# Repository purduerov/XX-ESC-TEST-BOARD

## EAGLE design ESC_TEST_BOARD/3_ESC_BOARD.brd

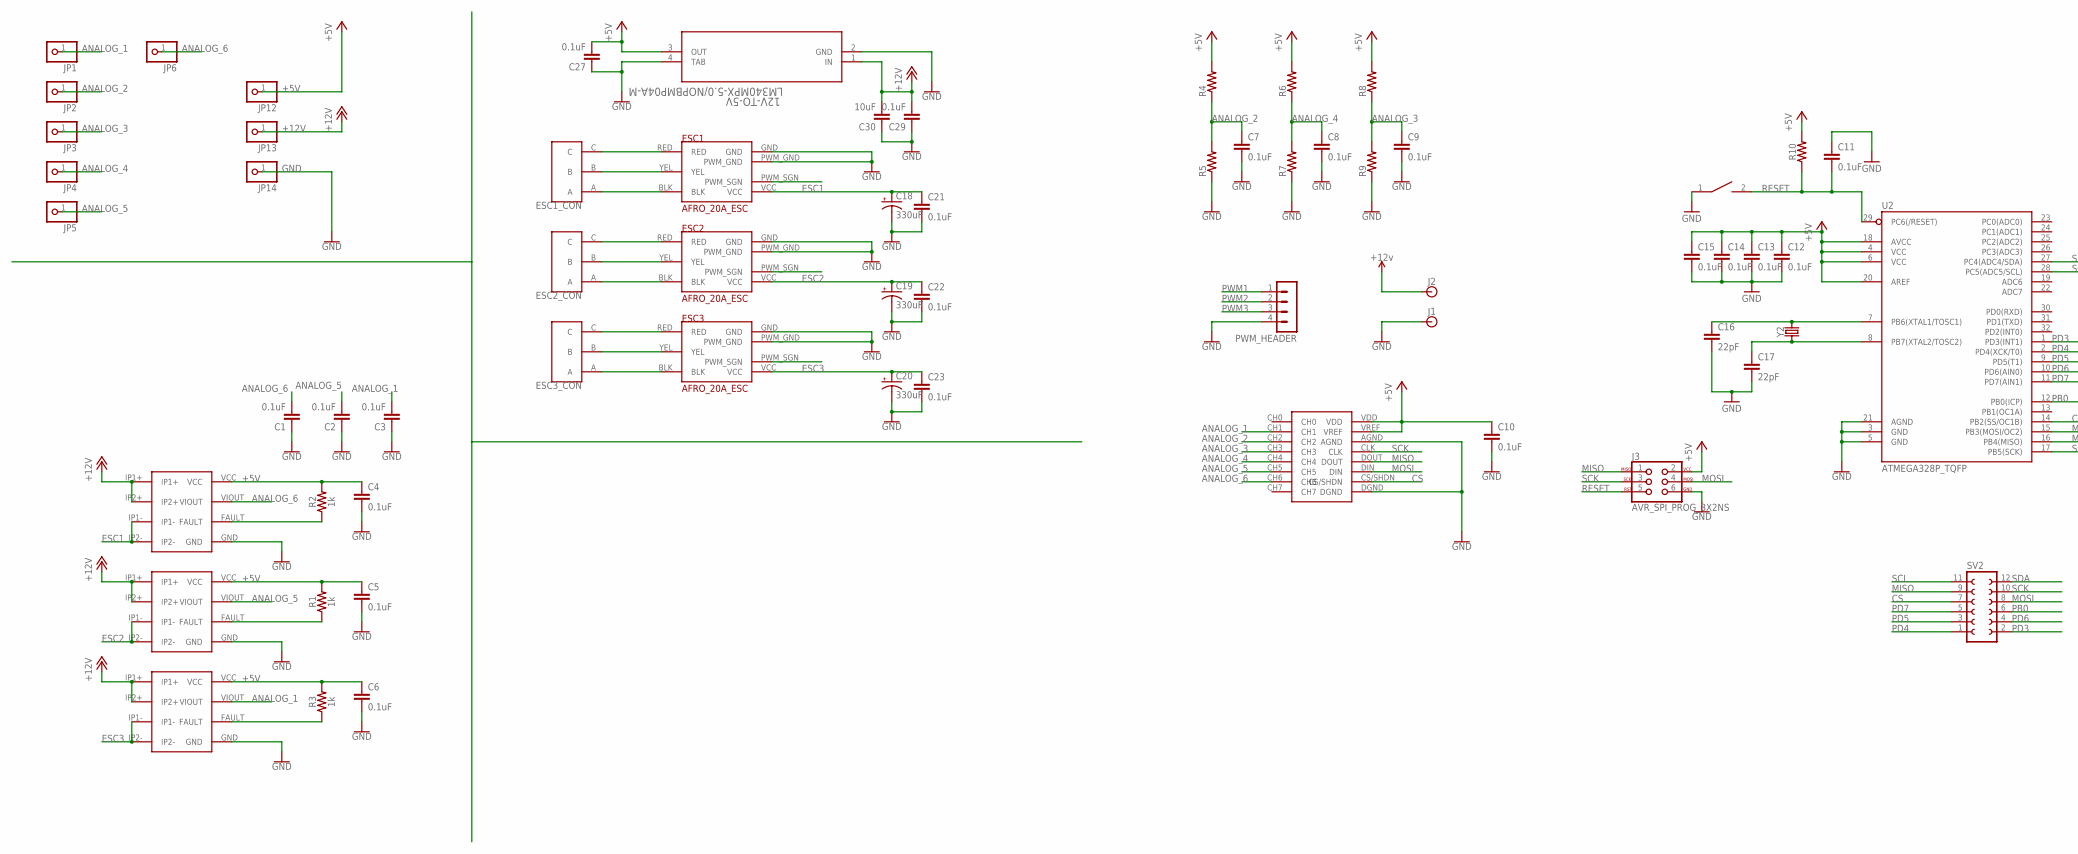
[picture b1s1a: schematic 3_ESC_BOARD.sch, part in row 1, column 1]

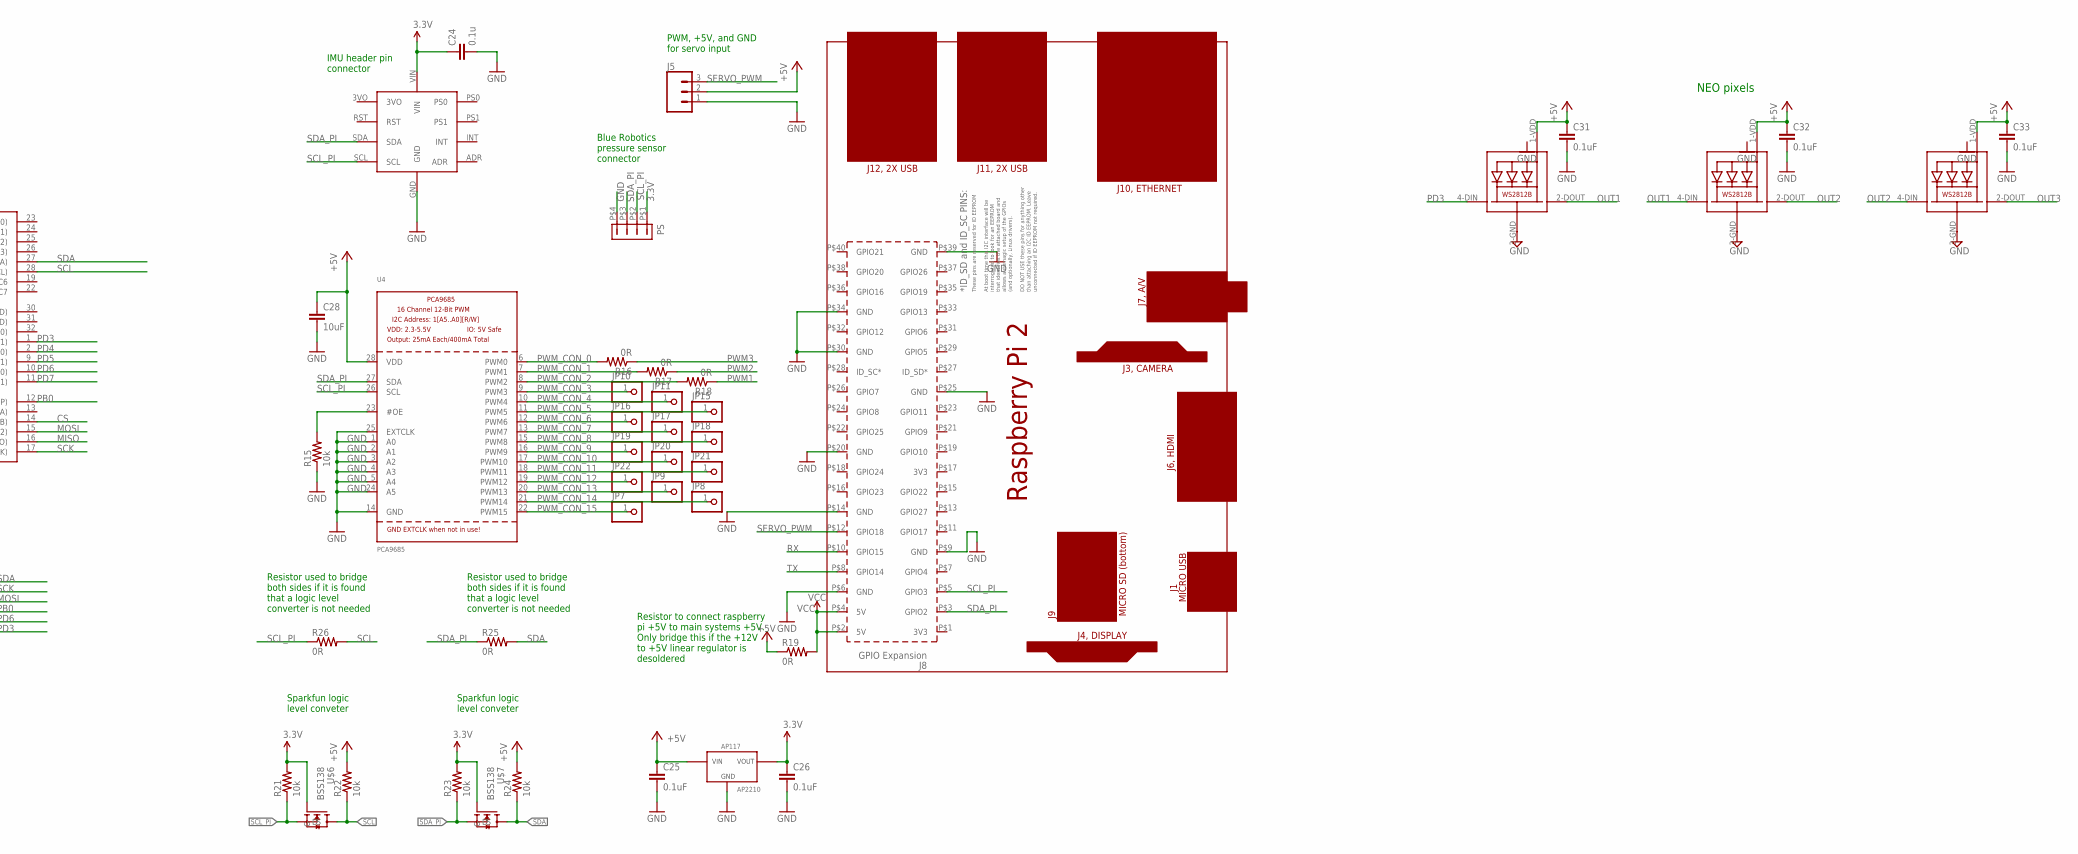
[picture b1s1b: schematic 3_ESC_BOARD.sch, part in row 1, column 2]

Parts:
12V-TO-5V: LM340MPX-5.0/NOPBMP04A-M; MP04A-M
C1, C2, C3, C4, C5, C6, C7, C8, C9, C10, C21, C22, C23, C25, C26, C27, C29: 0.1uF; 0603
C11, C12, C13, C14, C15, C31, C32, C33: 0.1uF; C0603
C16, C17: 22pF; C0603
C18, C19, C20: 330uF; CPOL-US(10.3_10.3MM)
C24: 0.1u; 0603-CAP
C28: 10uF; 0603-CAP
C30: 10uF; 0603
ESC1, ESC2, ESC3: AFRO_20A_ESC
ESC1_CON, ESC2_CON, ESC3_CON: 3PINCONNECTOR
J1, J2: BANANA_CONN
J3: AVR_SPI_PROG_3X2NS; 2X3-NS
J5: CONN_03; 1X03
JP1, JP2, JP3, JP4, JP5, JP6, JP7, JP8, JP9, JP10, JP11, JP12, JP13, JP14, JP15, JP16, JP17, JP18, JP19, JP20, JP21, JP22: PINHD-1X1; 1X01
LED1, LED2, LED3: WS2812B5050; WS2812B
PCB1: RPI2
PS: DF13-4P-1.25DSA
PWM_HEADER: MA04-1
R1, R2, R3: 1k; 0603
R4, R5, R6, R7, R8, R9: R-US_R0603; R0603
R10: 0603
R15: 10k; 0603-RES
R16, R17, R18, R19, R25, R26: 0R; 0603-RES
R21, R22, R23, R24: 10k; R0603
RESET: SWITCH; SW_2512
SV2: FE06-2
U2: ATMEGA328P_TQFP; TQFP32-08
U4: PCA9685; TSSOP28
U$1, U$2, U$3: ACS711
U$4: MCP3008
U$5: BNO055_9DOF_BREAKOUT; BNO055
U$6, U$7: BSS138
U$8: AP2210; SOT-23-3
Y2: CRYSTALPTH-HC49US; HC49US

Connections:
3.3V: C24.1, C26.1, PS.P$1 (1), R21.2, R23.2, U$5.VIN, U$6.G, U$7.G, U$8.VOUT
+5V: 12V-TO-5V.3 (OUT), C4.1, C5.1, C6.1, C10.1, C12.1, C13.1, C14.1, C15.1, C25.1, C27.2, C28.1, C31.1, C32.1, C33.1, J3.2, J5.2, JP12.1, LED1.1-VDD (VDD), LED2.1-VDD (VDD), LED3.1-VDD (VDD), R1.2, R2.2, R3.2, R4.2, R6.2, R8.2, R10.2, R19.1, R22.2, R24.2, U2.4 (VCC), U2.6 (VCC), U2.18 (AVCC), U2.20 (AREF), U4.28 (VDD), U$1.VCC, U$2.VCC, U$3.VCC, U$4.VDD, U$4.VREF, U$8.VIN
+12V: 12V-TO-5V.1 (IN), C29.2, C30.2, J2.P$1, JP13.1, U$1.IP1+, U$1.IP2+, U$2.IP1+, U$2.IP2+, U$3.IP1+, U$3.IP2+
ANALOG_1: C3.2, JP1.1, U$3.VIOUT, U$4.CH1
ANALOG_2: C7.1, JP2.1, R4.1, R5.2, U$4.CH2
ANALOG_3: C9.1, JP3.1, R8.1, R9.2, U$4.CH3
ANALOG_4: C8.1, JP4.1, R6.1, R7.2, U$4.CH4
ANALOG_5: C2.2, JP5.1, U$2.VIOUT, U$4.CH5
ANALOG_6: C1.2, JP6.1, U$1.VIOUT, U$4.CH6
CS: SV2.7, U2.14 (PB2(SS/OC1B)), U$4.CS/SHDN
ESC1: C18.+, C21.1, ESC1.VCC, U$1.IP1-, U$1.IP2-
ESC2: C19.+, C22.1, ESC2.VCC, U$2.IP1-, U$2.IP2-
ESC3: C20.+, C23.1, ESC3.VCC, U$3.IP1-, U$3.IP2-
GND: 12V-TO-5V.2 (GND), 12V-TO-5V.4 (TAB), C1.1, C2.1, C3.1, C4.2, C5.2, C6.2, C7.2, C8.2, C9.2, C10.2, C11.1, C12.2, C13.2, C14.2, C15.2, C16.2, C17.2, C18.-, C19.-, C20.-, C21.2, C22.2, C23.2, C24.2, C25.2, C26.2, C27.1, C28.2, C29.1, C30.1, C31.2, C32.2, C33.2, ESC1.GND, ESC1.PWM_GND, ESC2.GND, ESC2.PWM_GND, ESC3.GND, ESC3.PWM_GND, J1.P$1, J3.6, J5.1, JP14.1, LED1.3-GND (GND), LED2.3-GND (GND), LED3.3-GND (GND), PCB1.P$6 (GND), PCB1.P$9 (GND), PCB1.P$14 (GND), PCB1.P$20 (GND), PCB1.P$25 (GND), PCB1.P$30 (GND), PCB1.P$34 (GND), PCB1.P$39 (GND), PS.P$4 (4), PWM_HEADER.4, R5.1, R7.1, R9.1, R15.1, RESET.1, U2.3 (GND), U2.5 (GND), U2.21 (AGND), U4.1 (A0), U4.2 (A1), U4.3 (A2), U4.4 (A3), U4.5 (A4), U4.14 (GND), U4.24 (A5), U4.25 (EXTCLK), U$1.GND, U$2.GND, U$3.GND, U$4.AGND, U$4.DGND, U$5.GND, U$8.GND
MISO: J3.1, SV2.9, U2.16 (PB4(MISO)), U$4.DOUT
MOSI: J3.4, SV2.8, U2.15 (PB3(MOSI/OC2)), U$4.DIN
unnamed: ESC2.RED, ESC2_CON.C
unnamed: R2.1, U$1.FAULT
unnamed: ESC2.YEL, ESC2_CON.B
unnamed: R1.1, U$2.FAULT
unnamed: ESC2.BLK, ESC2_CON.A
unnamed: R3.1, U$3.FAULT
unnamed: ESC1.RED, ESC1_CON.C
unnamed: ESC1.YEL, ESC1_CON.B
unnamed: ESC1.BLK, ESC1_CON.A
unnamed: ESC3.RED, ESC3_CON.C
unnamed: ESC3.YEL, ESC3_CON.B
unnamed: ESC3.BLK, ESC3_CON.A
unnamed: C16.1, U2.7 (PB6(XTAL1/TOSC1)), Y2.2
unnamed: C17.1, U2.8 (PB7(XTAL2/TOSC2)), Y2.1
unnamed: R15.2, U4.23 (#OE)
OUT1: LED1.2-DOUT (DO), LED2.4-DIN (DI)
OUT2: LED2.2-DOUT (DO), LED3.4-DIN (DI)
OUT3: LED3.2-DOUT (DO)
PB0: SV2.6, U2.12 (PB0(ICP))
PD3: LED1.4-DIN (DI), SV2.2, U2.1 (PD3(INT1))
PD4: SV2.1, U2.2 (PD4(XCK/T0))
PD5: SV2.3, U2.9 (PD5(T1))
PD6: SV2.4, U2.10 (PD6(AIN0))
PD7: SV2.5, U2.11 (PD7(AIN1))
PWM1: ESC1.PWM_SGN, PWM_HEADER.1, R18.1
PWM2: ESC2.PWM_SGN, PWM_HEADER.2, R17.1
PWM3: ESC3.PWM_SGN, PWM_HEADER.3, R16.1
PWM_CON_0: R16.2, U4.6 (PWM0)
PWM_CON_1: R17.2, U4.7 (PWM1)
PWM_CON_2: R18.2, U4.8 (PWM2)
PWM_CON_3: JP10.1, U4.9 (PWM3)
PWM_CON_4: JP11.1, U4.10 (PWM4)
PWM_CON_5: JP15.1, U4.11 (PWM5)
PWM_CON_6: JP16.1, U4.12 (PWM6)
PWM_CON_7: JP17.1, U4.13 (PWM7)
PWM_CON_8: JP18.1, U4.15 (PWM8)
PWM_CON_9: JP19.1, U4.16 (PWM9)
PWM_CON_10: JP20.1, U4.17 (PWM10)
PWM_CON_11: JP21.1, U4.18 (PWM11)
PWM_CON_12: JP22.1, U4.19 (PWM12)
PWM_CON_13: JP9.1, U4.20 (PWM13)
PWM_CON_14: JP8.1, U4.21 (PWM14)
PWM_CON_15: JP7.1, U4.22 (PWM15)
RESET: C11.2, J3.5, R10.1, RESET.2, U2.29 (PC6(/RESET))
RX: PCB1.P$10 (GPIO15)
SCK: J3.3, SV2.10, U2.17 (PB5(SCK)), U$4.CLK
SCL: R22.1, R26.2, SV2.11, U2.28 (PC5(ADC5/SCL)), U$6.D
SCL_PI: PCB1.P$5 (GPIO3), PS.P$2 (2), R21.1, R26.1, U4.26 (SCL), U$5.SCL, U$6.S
SDA: R24.1, R25.2, SV2.12, U2.27 (PC4(ADC4/SDA)), U$7.D
SDA_PI: PCB1.P$3 (GPIO2), PS.P$3 (3), R23.1, R25.1, U4.27 (SDA), U$5.SDA, U$7.S
SERVO_PWM: J5.3, PCB1.P$12 (GPIO18)
TX: PCB1.P$8 (GPIO14)
VCC: PCB1.P$2 (5V), PCB1.P$4 (5V), R19.2

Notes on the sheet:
Resistor used to bridge both sides if it is found that a logic level converter is not needed
Sparkfun logic level conveter
PWM, +5V, and GND for servo input
Blue Robotics pressure sensor connector
IMU header pin connector
Resistor to connect raspberry pi +5V to main systems +5V. Only bridge this if the +12V to +5V linear regulator is desoldered
NEO pixels

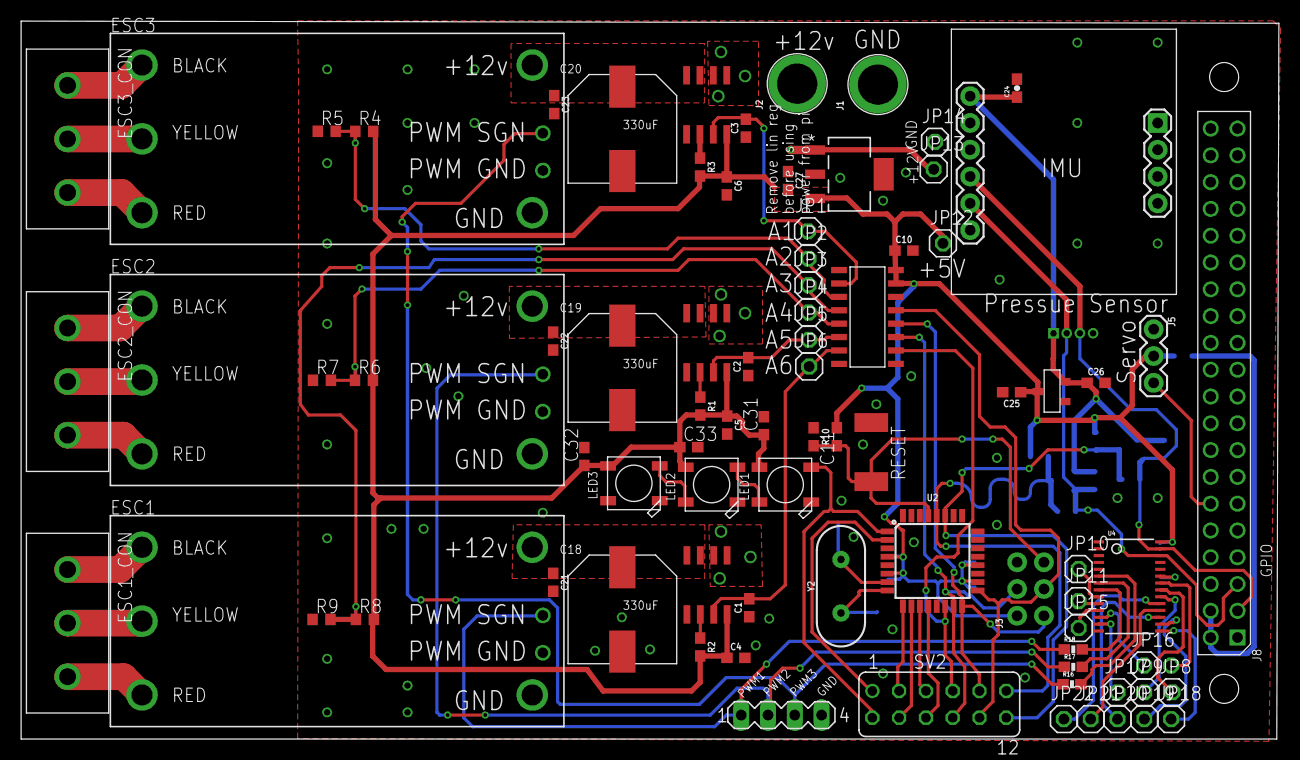
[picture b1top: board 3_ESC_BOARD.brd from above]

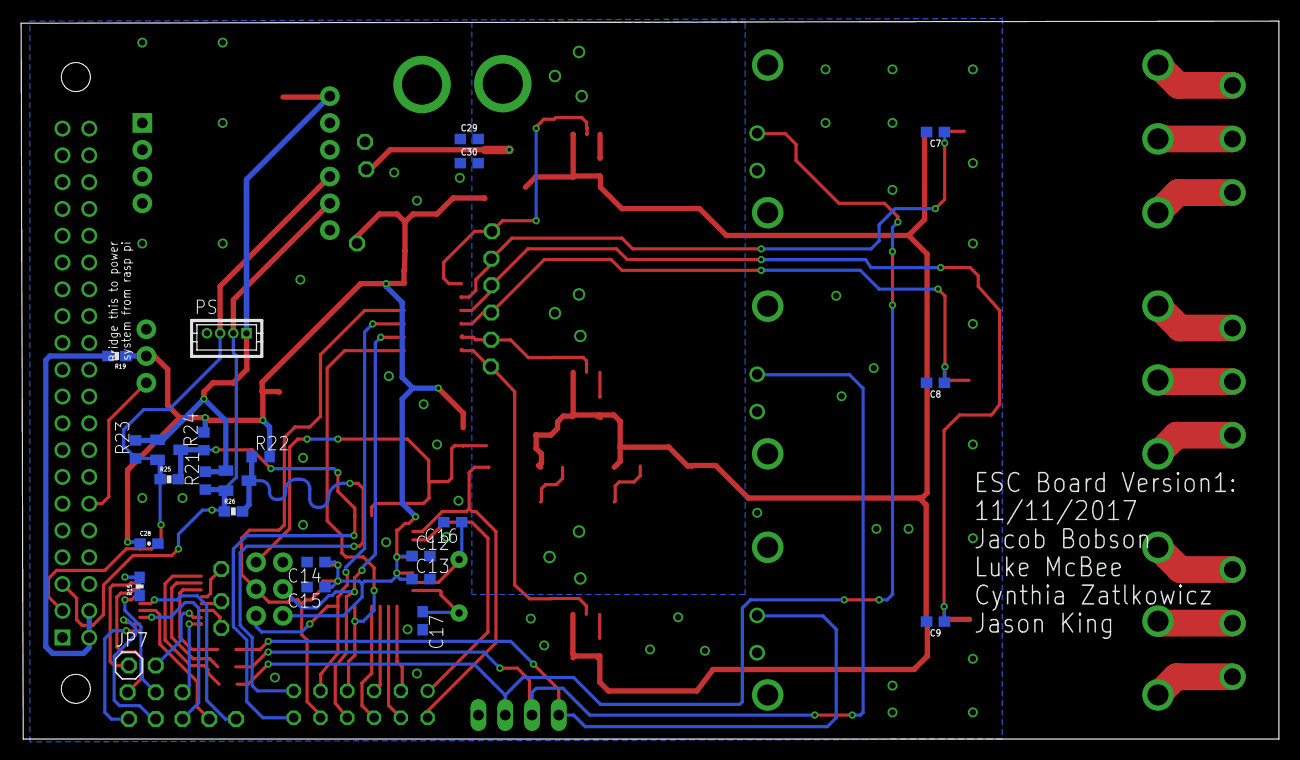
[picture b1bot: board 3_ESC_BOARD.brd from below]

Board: 2 copper layers, 119.2 x 68.1 mm, 106 parts (24 on the bottom side), 66 nets.

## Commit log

2017-10-27 Inital commit
2017-10-28 Finshing out circuit board
2017-11-02 Removed backup files, moved parts
2017-11-02 Saving before autoroute
2017-11-11 Updating ESC Test Board
2017-11-11 Almost done with initial routing
2017-11-11 Finished routing of Jacobs section
2017-11-12 Finished adding the raspberry pi portion of the circuit board.
2017-11-13 Addressing comments made by Kyle and Carolyn
2017-11-14 Added capacitor values to unmarked capacitors
2017-11-16 fixed oscillator trace lengths and miso via
2017-11-16 Exported BOM

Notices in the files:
parts and their libraries:
SparkFun-Connectors: Licensing: Creative Commons ShareAlike 4.0 International - https://creativecommons.org/licenses/by-sa/4.0
